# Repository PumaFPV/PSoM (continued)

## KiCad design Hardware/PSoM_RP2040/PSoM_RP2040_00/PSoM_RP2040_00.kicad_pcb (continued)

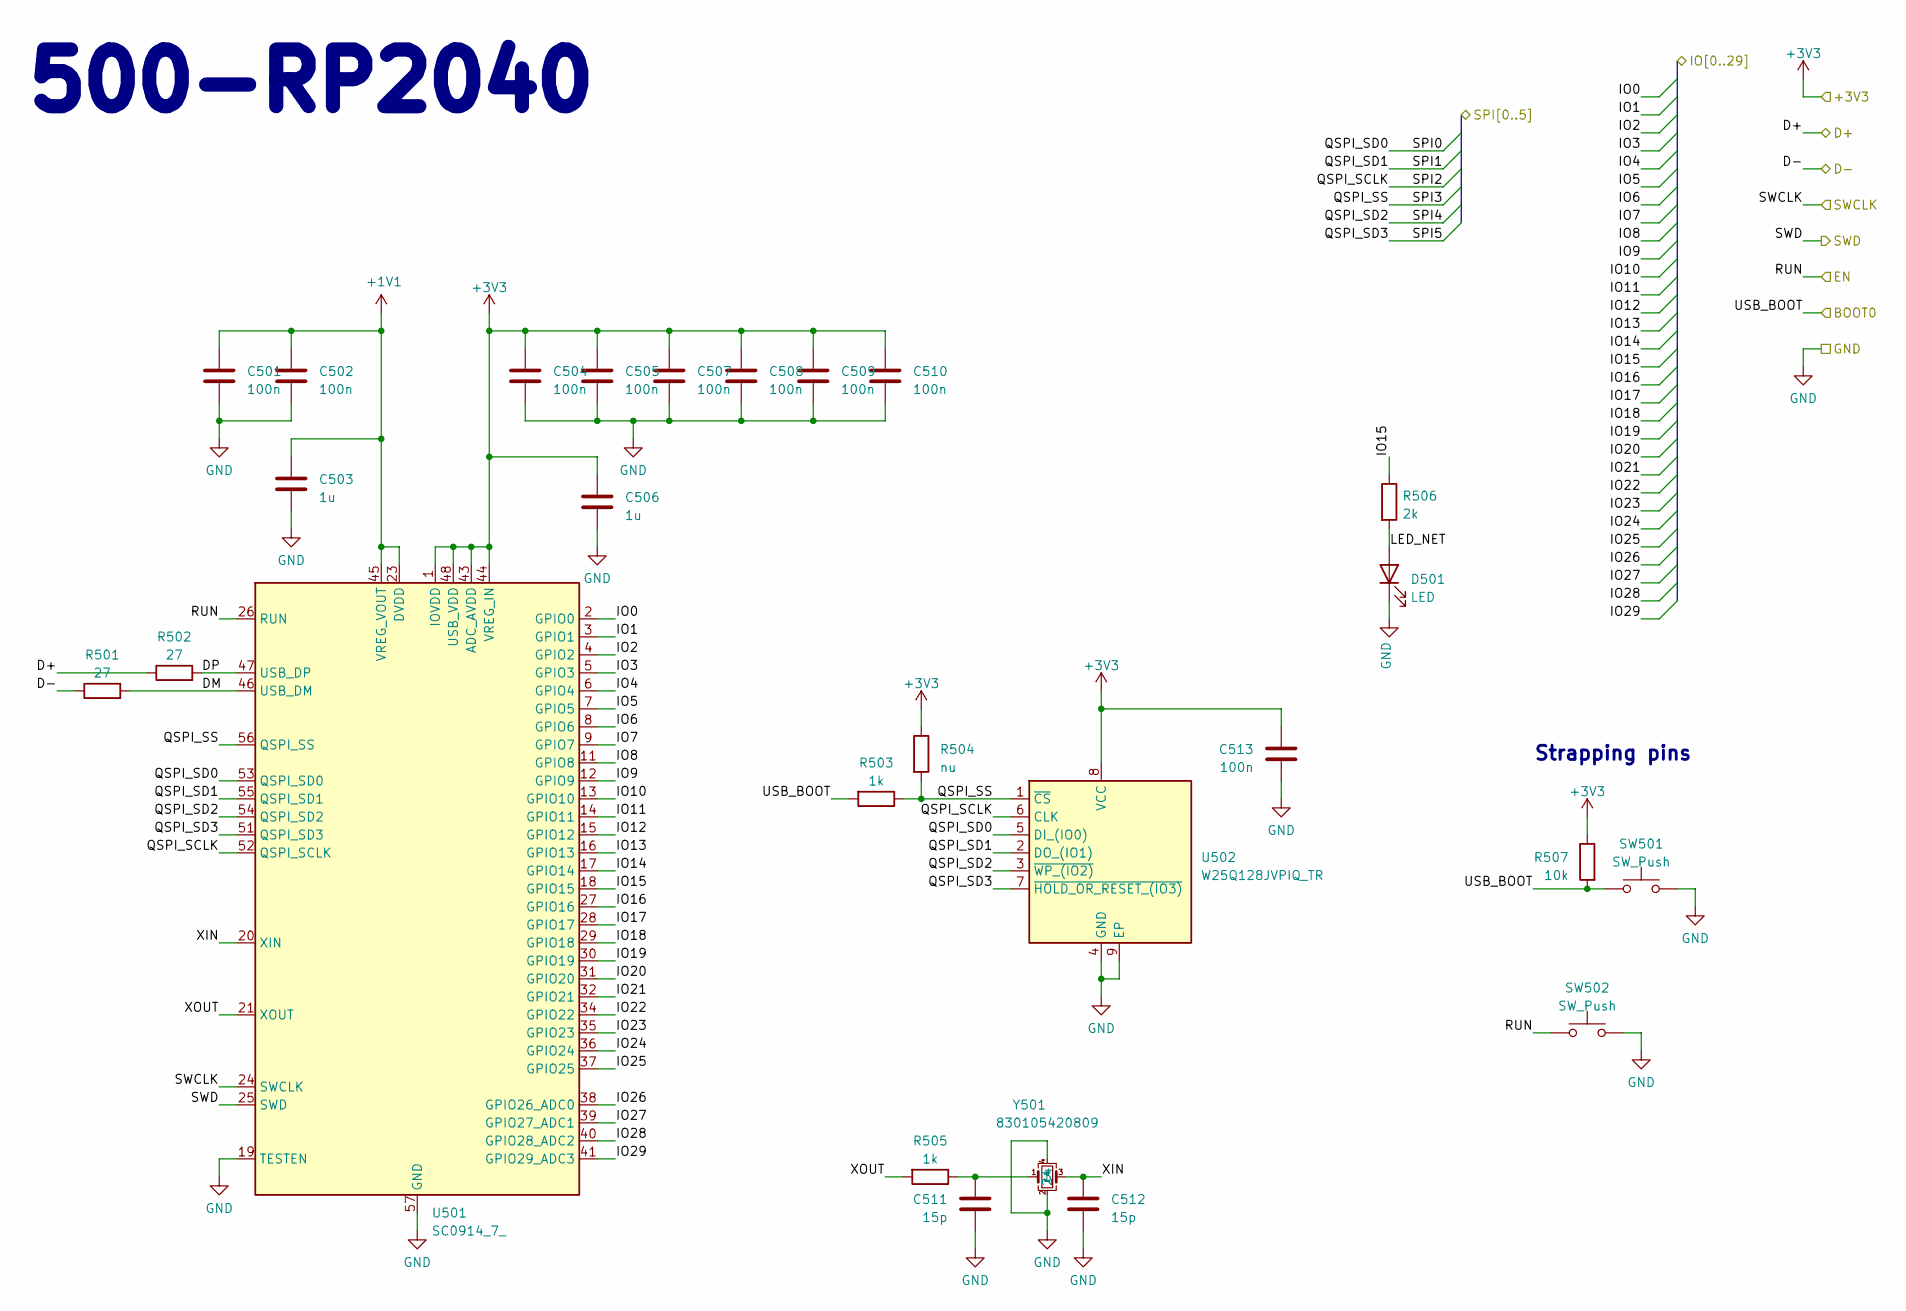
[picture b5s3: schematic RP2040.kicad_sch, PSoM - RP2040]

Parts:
C501, C502, C504, C505, C507, C508, C509, C510, C513: 100n; C_0201_0603Metric
C503, C506: 1u; C_0402_1005Metric
C511, C512: 15p; C_0201_0603Metric
D501: LED; LED_0402_1005Metric
R501, R502: 27; R_0201_0603Metric
R503, R505: 1k; R_0201_0603Metric
R504: nu; R_0201_0603Metric
R506: 2k; R_0402_1005Metric
R507: 10k; R_0201_0603Metric
SW501, SW502: SW_Push; B3U-1000P
U501: SC0914_7_; QFN40P700X700X90-57N-D; Mouser Part Number 358-SC09147
U502: W25Q128JVPIQ_TR; SON127P600X500X80-9N-D; Mouser Part Number 454-W25Q128JVPIQTR
Y501: 830105420809; Mouser Part Number 710-830105420809

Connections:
+1V1: C501.1, C502.1, C503.1, U501.23 (DVDD), U501.45 (VREG_VOUT), U501.50 (DVDD)
+3V3: C504.1, C505.1, C506.1, C507.1, C508.1, C509.1, C510.1, C513.1, R504.1, R507.1, U501.1 (IOVDD), U501.10 (IOVDD), U501.22 (IOVDD), U501.33 (IOVDD), U501.42 (IOVDD), U501.43 (ADC_AVDD), U501.44 (VREG_IN), U501.48 (USB_VDD), U501.49 (IOVDD), U502.8 (VCC); also elsewhere on the board
/200_Connectors/BOOT0: R503.2, R507.2, SW501.1
/200_Connectors/D+: R502.1; also elsewhere on the board
/200_Connectors/D-: R501.1; also elsewhere on the board
/200_Connectors/EN: SW502.1, U501.26 (RUN); also elsewhere on the board
/200_Connectors/SWCLK: U501.24 (SWCLK); also elsewhere on the board
/200_Connectors/SWD: U501.25 (SWD); also elsewhere on the board
/500_RP2040/DM: R501.2, U501.46 (USB_DM)
/500_RP2040/DP: R502.2, U501.47 (USB_DP)
/500_RP2040/LED_NET: D501.2 (A), R506.2
/500_RP2040/XIN: C512.1, U501.20 (XIN), Y501.3
/500_RP2040/XOUT: R505.2, U501.21 (XOUT)
IO0: U501.2 (GPIO0); also elsewhere on the board
IO1: U501.3 (GPIO1); also elsewhere on the board
IO2: U501.4 (GPIO2); also elsewhere on the board
IO3: U501.5 (GPIO3); also elsewhere on the board
IO4: U501.6 (GPIO4); also elsewhere on the board
IO5: U501.7 (GPIO5); also elsewhere on the board
IO6: U501.8 (GPIO6); also elsewhere on the board
IO7: U501.9 (GPIO7); also elsewhere on the board
IO8: U501.11 (GPIO8); also elsewhere on the board
IO9: U501.12 (GPIO9); also elsewhere on the board
IO10: U501.13 (GPIO10); also elsewhere on the board
IO11: U501.14 (GPIO11); also elsewhere on the board
IO12: U501.15 (GPIO12); also elsewhere on the board
IO13: U501.16 (GPIO13); also elsewhere on the board
IO14: U501.17 (GPIO14); also elsewhere on the board
IO15: R506.1, U501.18 (GPIO15); also elsewhere on the board
IO16: U501.27 (GPIO16); also elsewhere on the board
IO17: U501.28 (GPIO17); also elsewhere on the board
IO18: U501.29 (GPIO18); also elsewhere on the board
IO19: U501.30 (GPIO19); also elsewhere on the board
IO20: U501.31 (GPIO20); also elsewhere on the board
IO21: U501.32 (GPIO21); also elsewhere on the board
IO22: U501.34 (GPIO22); also elsewhere on the board
IO23: U501.35 (GPIO23); also elsewhere on the board
IO24: U501.36 (GPIO24); also elsewhere on the board
IO25: U501.37 (GPIO25); also elsewhere on the board
IO26: U501.38 (GPIO26_ADC0); also elsewhere on the board
IO27: U501.39 (GPIO27_ADC1); also elsewhere on the board
IO28: U501.40 (GPIO28_ADC2); also elsewhere on the board
unnamed: C511.1, R505.1, Y501.1
SPI0: U501.53 (QSPI_SD0), U502.5 (DI_(IO0)); also elsewhere on the board
SPI1: U501.55 (QSPI_SD1), U502.2 (DO_(IO1)); also elsewhere on the board
SPI2: U501.52 (QSPI_SCLK), U502.6 (CLK); also elsewhere on the board
SPI3: R503.1, R504.2, U501.56 (QSPI_SS), U502.1 (~CS); also elsewhere on the board
SPI4: U501.54 (QSPI_SD2), U502.3 (~WP_(IO2)); also elsewhere on the board
SPI5: U501.51 (QSPI_SD3), U502.7 (~HOLD_OR_RESET_(IO3)); also elsewhere on the board

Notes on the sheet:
500-RP2040
Strapping pins

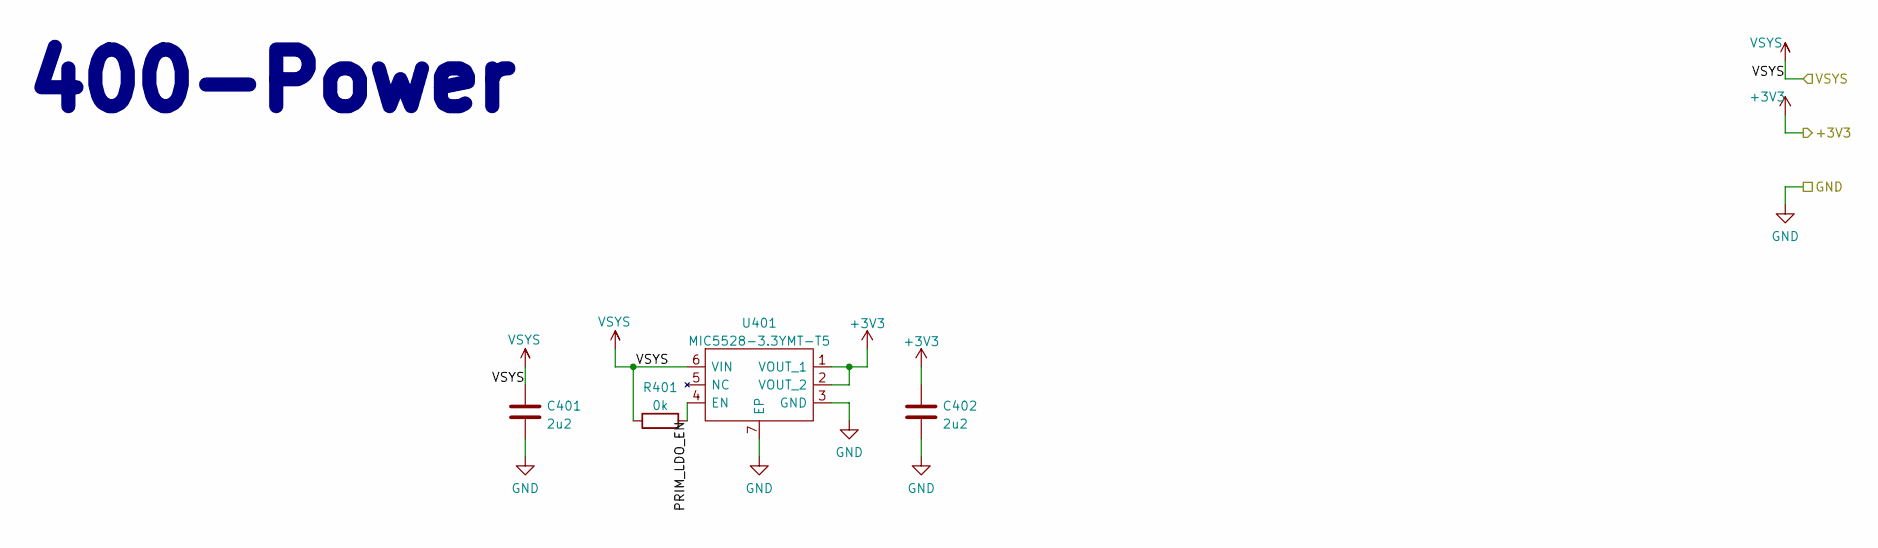
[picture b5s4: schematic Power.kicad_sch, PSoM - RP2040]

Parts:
C401, C402: 2u2; C_0603_1608Metric
R401: 0k; R_0201_0603Metric
U401: MIC5528-3.3YMT-T5; SON40P120X120X60-7N-D; Mouser Part Number 998-MIC5528-3.3YMTT5

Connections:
+3V3: C402.1, U401.1 (VOUT_1), U401.2 (VOUT_2); also elsewhere on the board
/400_Power/PRIM_LDO_EN: R401.2, U401.4 (EN)
/VSYS: C401.1, R401.1, U401.6 (VIN); also elsewhere on the board

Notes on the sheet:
400-Power

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
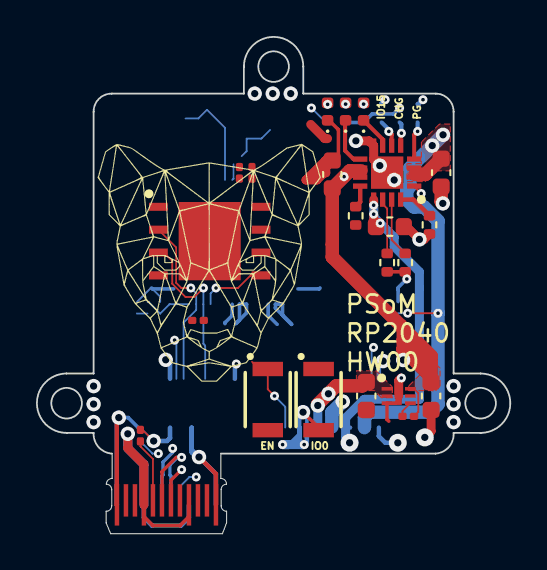
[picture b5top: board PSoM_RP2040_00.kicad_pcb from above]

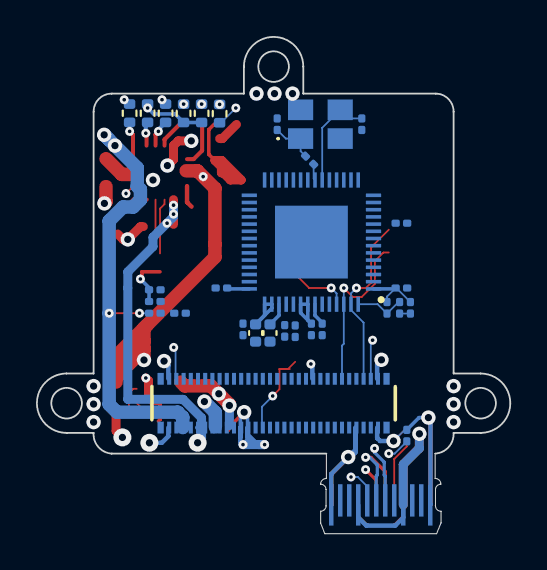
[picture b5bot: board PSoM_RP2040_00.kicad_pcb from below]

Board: 6 copper layers, 26.3 x 27.6 mm, 53 parts (30 on the bottom side), 70 nets.

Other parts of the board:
C201: 100n; C_0201_0603Metric

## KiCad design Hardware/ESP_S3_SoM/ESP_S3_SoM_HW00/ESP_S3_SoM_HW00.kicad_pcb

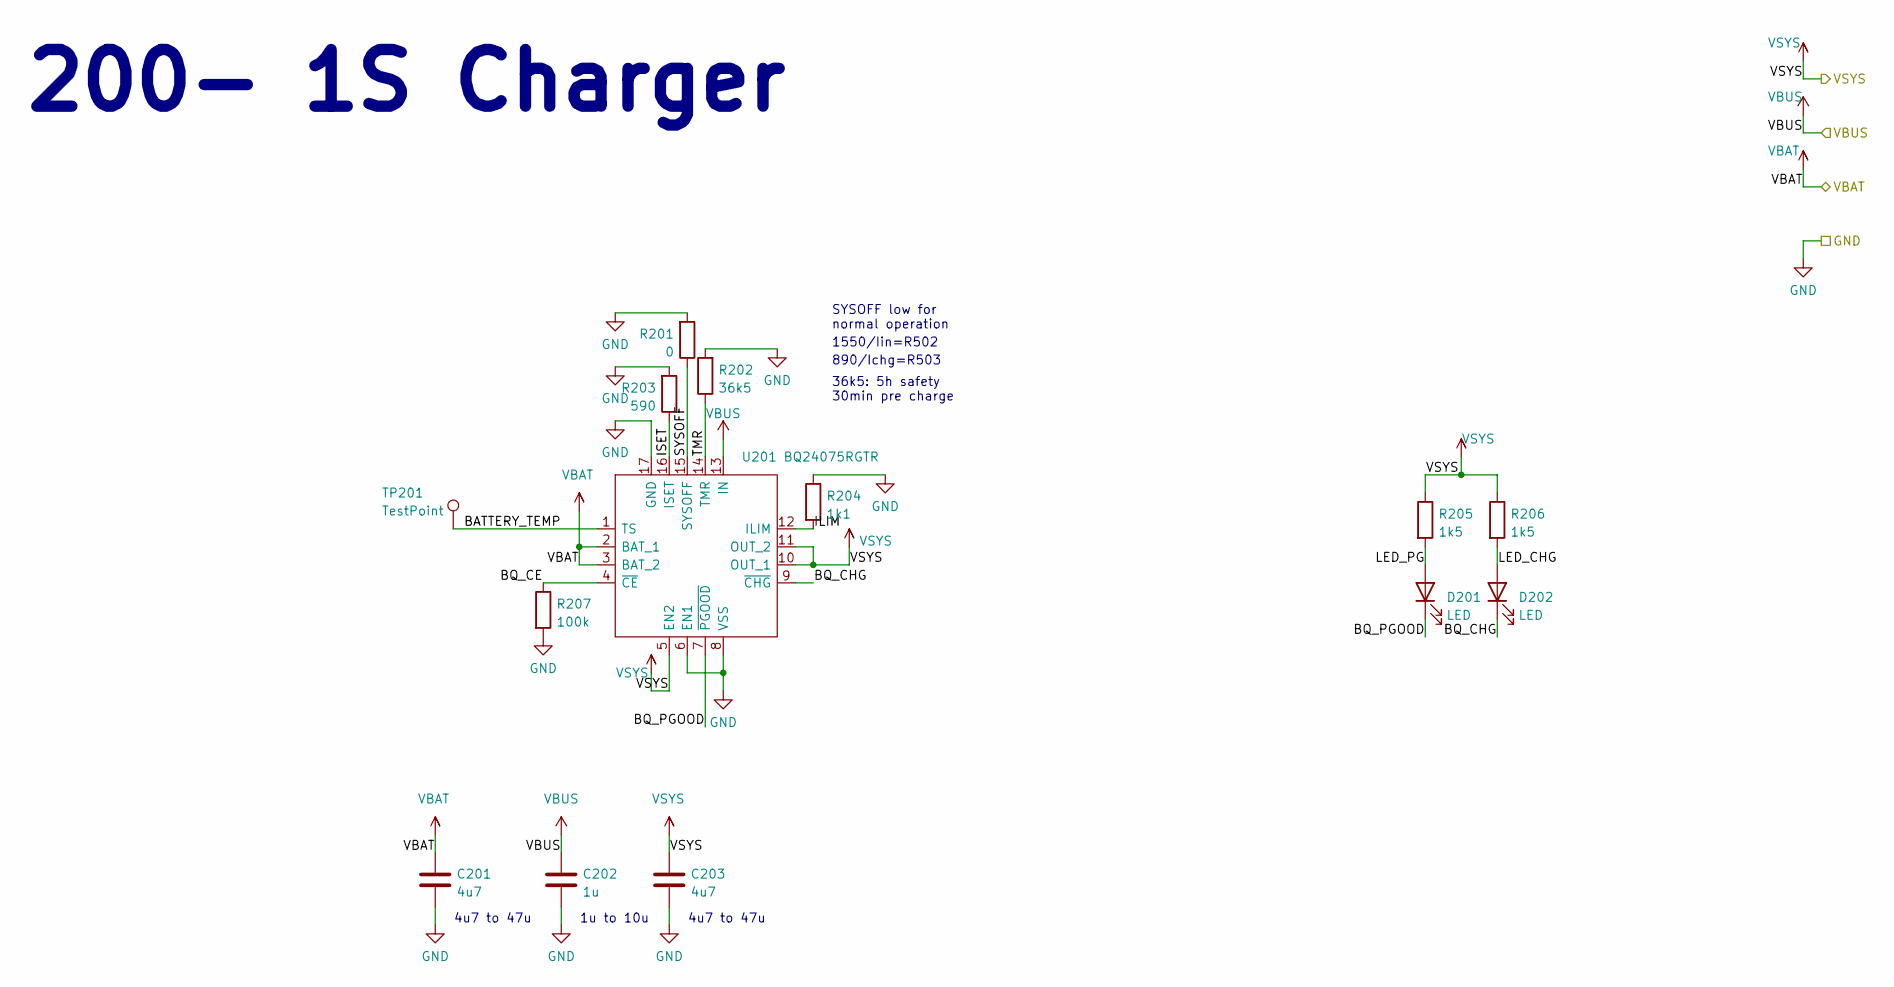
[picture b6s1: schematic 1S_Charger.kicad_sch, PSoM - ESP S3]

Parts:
C201, C203: 4u7; C_0603_1608Metric
C202: 1u; C_0603_1608Metric
D201, D202: LED; LED_0402_1005Metric_DUALSIDE
R201: 0; R_0402_1005Metric
R202: 36k5; R_0402_1005Metric
R203: 590; R_0402_1005Metric
R204: 1k1; R_0402_1005Metric
R205, R206: 1k5; R_0402_1005Metric
R207: 100k; R_0402_1005Metric
TP201: TestPoint; TestPoint_Pad_D1.0mm
U201: BQ24075RGTR; QFN50P300X300X100-17N-D; Mouser Part Number 595-BQ24075RGTR

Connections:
/200_1S_Charger/BATTERY_TEMP: TP201.1, U201.1 (TS)
/200_1S_Charger/BQ_CE: R207.1, U201.4 (~CE)
/200_1S_Charger/BQ_CHG: D202.1 (K), U201.9 (~CHG)
/200_1S_Charger/BQ_PGOOD: D201.1 (K), U201.7 (~PGOOD)
/200_1S_Charger/ILIM: R204.2, U201.12 (ILIM)
/200_1S_Charger/ISET: R203.1, U201.16 (ISET)
/200_1S_Charger/LED_CHG: D202.2 (A), R206.2
/200_1S_Charger/LED_PG: D201.2 (A), R205.2
/200_1S_Charger/SYSOFF: R201.1, U201.15 (SYSOFF)
/200_1S_Charger/TMR: R202.1, U201.14 (TMR)
/200_1S_Charger/VBAT: C201.1, U201.2 (BAT_1), U201.3 (BAT_2)
/200_1S_Charger/VSYS: C203.1, R205.1, R206.1, U201.5 (EN2), U201.10 (OUT_1), U201.11 (OUT_2)
GND: C201.2, C202.2, C203.2, R201.2, R202.2, R203.2, R204.1, R207.2, U201.6 (EN1), U201.8 (VSS), U201.17 (GND); also elsewhere on the board
VBUS: C202.1, U201.13 (IN); also elsewhere on the board

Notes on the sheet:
890/Ichg=R503
200- 1S Charger
4u7 to 47u
1u to 10u
SYSOFF low for normal operation
36k5: 5h safety 30min pre charge
1550/Iin=R502

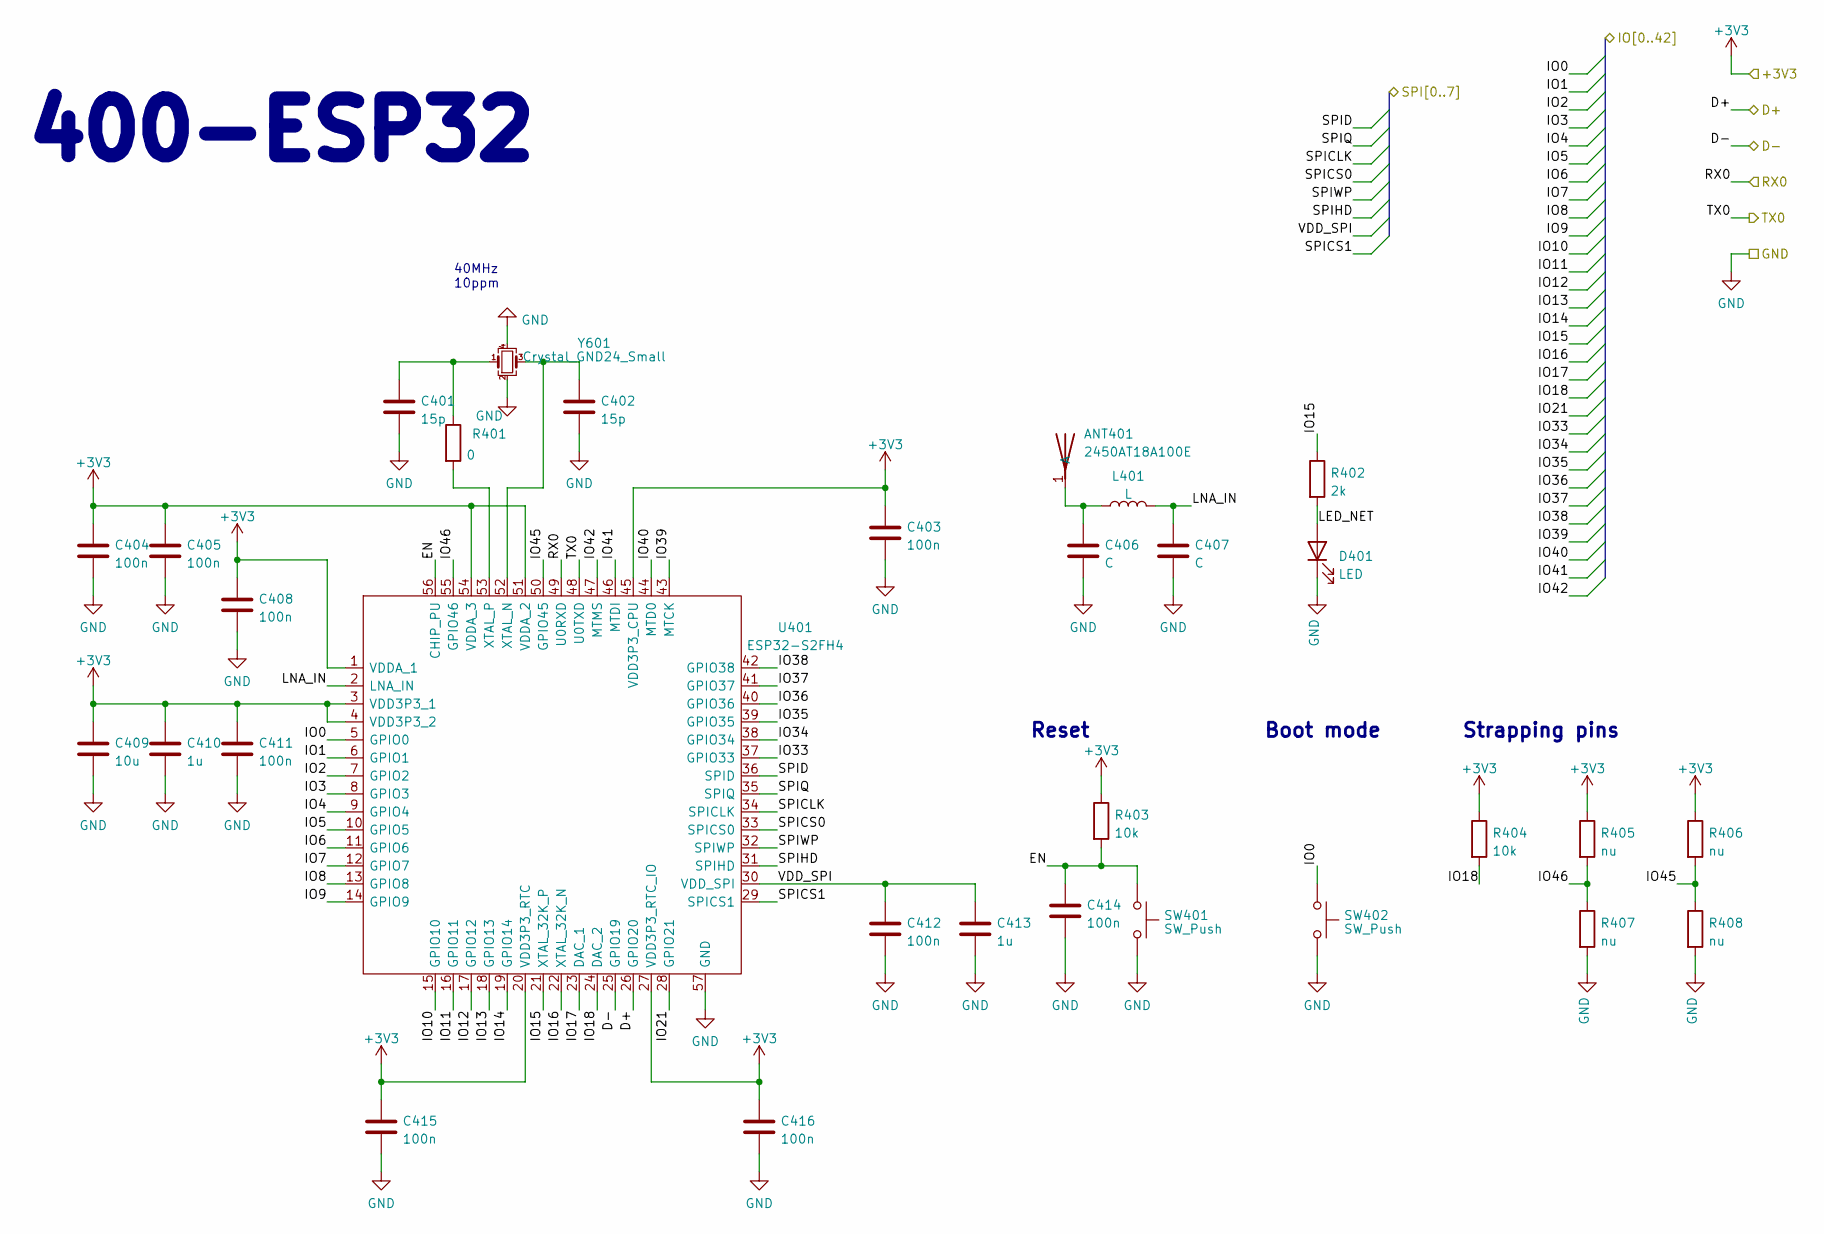
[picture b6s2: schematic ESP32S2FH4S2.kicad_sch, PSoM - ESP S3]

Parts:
ANT401: 2450AT18A100E; ANTC3216X140N; Mouser Part Number 609-2450AT18A100E
C401, C402: 15p; C_0201_0603Metric
C403, C404, C405, C408, C411, C412, C414, C415, C416: 100n; C_0402_1005Metric
C406, C407: C; C_0201_0603Metric
C409: 10u; C_0603_1608Metric
C410, C413: 1u; C_0402_1005Metric
D401: LED; LED_0402_1005Metric_DUALSIDE
L401: L; L_0201_0603Metric
R401: 0; R_0201_0603Metric
R402: 2k; R_0402_1005Metric
R403, R404: 10k; R_0201_0603Metric
R405, R406, R407, R408: nu; R_0201_0603Metric
SW401, SW402: SW_Push; B3U-1000P
U401: ESP32-S2FH4; QFN40P700X700X90-57N-D; Mouser Part Number 356-ESP32-S2FH4
Y601: Crystal_GND24_Small; Crystal_SMD_2016-4Pin_2.0x1.6mm

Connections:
+3V3: C403.1, C404.1, C405.1, C408.1, C409.1, C410.1, C411.1, C415.1, C416.1, R403.1, R404.1, R405.1, R406.1, U401.1 (VDDA_1), U401.3 (VDD3P3_1), U401.4 (VDD3P3_2), U401.20 (VDD3P3_RTC), U401.27 (VDD3P3_RTC_IO), U401.45 (VDD3P3_CPU), U401.51 (VDDA_2), U401.54 (VDDA_3); also elsewhere on the board
/100_Connectors/D+: U401.26 (GPIO20); also elsewhere on the board
/100_Connectors/D-: U401.25 (GPIO19); also elsewhere on the board
/100_Connectors/RX0: U401.49 (U0RXD); also elsewhere on the board
/100_Connectors/TX0: U401.48 (U0TXD); also elsewhere on the board
/400_ESP32/EN: C414.1, R403.2, SW401.1, U401.56 (CHIP_PU)
/400_ESP32/IO45: R406.2, R408.1, U401.50 (GPIO45)
/400_ESP32/IO46: R405.2, R407.1, U401.55 (GPIO46)
/400_ESP32/LED_NET: D401.2 (A), R402.2
/400_ESP32/LNA_IN: C407.1, L401.2, U401.2 (LNA_IN)
/400_ESP32/SPICLK: U401.34 (SPICLK)
/400_ESP32/SPICS0: U401.33 (SPICS0)
/400_ESP32/SPICS1: U401.29 (SPICS1)
/400_ESP32/SPID: U401.36 (SPID)
/400_ESP32/SPIHD: U401.31 (SPIHD)
/400_ESP32/SPIQ: U401.35 (SPIQ)
/400_ESP32/SPIWP: U401.32 (SPIWP)
/400_ESP32/VDD_SPI: C412.1, C413.1, U401.30 (VDD_SPI)
GND: C401.2, C402.2, C403.2, C404.2, C405.2, C406.2, C407.2, C408.2, C409.2, C410.2, C411.2, C412.2, C413.2, C414.2, C415.2, C416.2, D401.1 (K), R407.2, R408.2, SW401.2, SW402.2, U401.57 (GND), Y601.2, Y601.4; also elsewhere on the board
IO0: SW402.1, U401.5 (GPIO0); also elsewhere on the board
IO1: U401.6 (GPIO1); also elsewhere on the board
IO2: U401.7 (GPIO2); also elsewhere on the board
IO3: U401.8 (GPIO3); also elsewhere on the board
IO4: U401.9 (GPIO4); also elsewhere on the board
IO5: U401.10 (GPIO5); also elsewhere on the board
IO6: U401.11 (GPIO6); also elsewhere on the board
IO7: U401.12 (GPIO7); also elsewhere on the board
IO8: U401.13 (GPIO8); also elsewhere on the board
IO9: U401.14 (GPIO9); also elsewhere on the board
IO10: U401.15 (GPIO10); also elsewhere on the board
IO11: U401.16 (GPIO11); also elsewhere on the board
IO12: U401.17 (GPIO12); also elsewhere on the board
IO13: U401.18 (GPIO13); also elsewhere on the board
IO14: U401.19 (GPIO14); also elsewhere on the board
IO15: R402.1, U401.21 (XTAL_32K_P); also elsewhere on the board
IO16: U401.22 (XTAL_32K_N); also elsewhere on the board
IO17: U401.23 (DAC_1); also elsewhere on the board
IO18: R404.2, U401.24 (DAC_2); also elsewhere on the board
IO21: U401.28 (GPIO21); also elsewhere on the board
IO33: U401.37 (GPIO33); also elsewhere on the board
IO34: U401.38 (GPIO34); also elsewhere on the board
IO35: U401.39 (GPIO35); also elsewhere on the board
IO36: U401.40 (GPIO36); also elsewhere on the board
IO37: U401.41 (GPIO37); also elsewhere on the board
IO38: U401.42 (GPIO38); also elsewhere on the board
IO39: U401.43 (MTCK); also elsewhere on the board
IO40: U401.44 (MTD0); also elsewhere on the board
IO41: U401.46 (MTDI); also elsewhere on the board
IO42: U401.47 (MTMS); also elsewhere on the board
unnamed: ANT401.1 (A), C406.1, L401.1
unnamed: C401.1, R401.1, Y601.1
unnamed: C402.1, U401.52 (XTAL_N), Y601.3
unnamed: R401.2, U401.53 (XTAL_P)

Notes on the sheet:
Boot mode
Reset
40MHz 10ppm
400-ESP32
Strapping pins

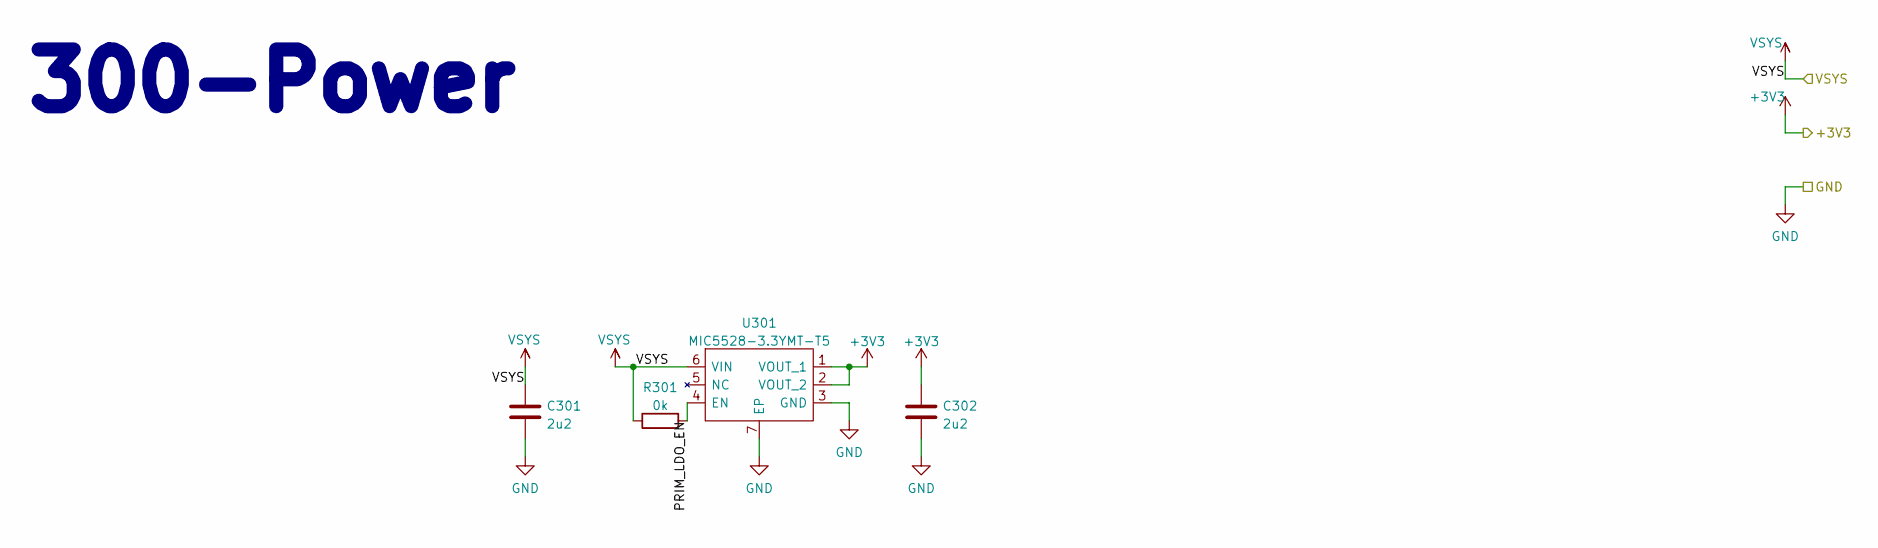
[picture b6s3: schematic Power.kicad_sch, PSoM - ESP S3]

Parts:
C301, C302: 2u2; C_0603_1608Metric
R301: 0k; R_0201_0603Metric
U301: MIC5528-3.3YMT-T5; SON40P120X120X60-7N-D; Mouser Part Number 998-MIC5528-3.3YMTT5

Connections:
+3V3: C302.1, U301.1 (VOUT_1), U301.2 (VOUT_2); also elsewhere on the board
/300_Power/PRIM_LDO_EN: R301.2, U301.4 (EN)
/300_Power/VSYS: C301.1, R301.1, U301.6 (VIN)
GND: C301.2, C302.2, U301.3 (GND), U301.7 (EP); also elsewhere on the board

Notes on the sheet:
300-Power

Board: 2 copper layers, 53 parts (1 on the bottom side), 65 nets, no tracks yet.

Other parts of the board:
J101: USB4510-03-1-A; USB4510031A
J102: 54722-0604; 547220604
R101, R102: 5.1k; R_0201_0603Metric

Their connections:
+3V3: J102.4, J102.6; also elsewhere on the board
/100_Connectors/CC1: J101.A5 (CC1), R102.1
/100_Connectors/CC2: J101.B5 (CC2), R101.1
/100_Connectors/D+: J101.A6 (D+), J101.B6 (D+), J102.58; also elsewhere on the board
/100_Connectors/D-: J101.A7 (D-), J101.B7 (D-), J102.57; also elsewhere on the board
/100_Connectors/RX0: J102.13; also elsewhere on the board
/100_Connectors/TX0: J102.15; also elsewhere on the board
/100_Connectors/VBAT: J102.7, J102.9
/100_Connectors/VSYS: J102.8, J102.10
GND: J101.A1 (GND), J101.A12 (GND), J101.MH1, J101.MH2, J101.MH3, J101.MH4, J102.1, J102.2, J102.11, J102.12, J102.55, J102.56, J102.59, J102.60, R101.2, R102.2; also elsewhere on the board
IO0: J102.14; also elsewhere on the board
IO1: J102.16; also elsewhere on the board
IO2: J102.18; also elsewhere on the board
IO3: J102.20; also elsewhere on the board
IO4: J102.22; also elsewhere on the board
IO5: J102.24; also elsewhere on the board
IO6: J102.26; also elsewhere on the board
IO7: J102.28; also elsewhere on the board
IO8: J102.30; also elsewhere on the board
IO9: J102.32; also elsewhere on the board
IO10: J102.34; also elsewhere on the board
IO11: J102.36; also elsewhere on the board
IO12: J102.38; also elsewhere on the board
IO13: J102.40; also elsewhere on the board
IO14: J102.42; also elsewhere on the board
IO15: J102.44; also elsewhere on the board
IO16: J102.46; also elsewhere on the board
IO17: J102.48; also elsewhere on the board
IO18: J102.50; also elsewhere on the board
IO21: J102.52; also elsewhere on the board
IO33: J102.54; also elsewhere on the board
IO34: J102.37; also elsewhere on the board
IO35: J102.39; also elsewhere on the board
IO36: J102.41; also elsewhere on the board
IO37: J102.43; also elsewhere on the board
IO38: J102.45; also elsewhere on the board
IO39: J102.47; also elsewhere on the board
IO40: J102.49; also elsewhere on the board
IO41: J102.51; also elsewhere on the board
IO42: J102.53; also elsewhere on the board
VBUS: J101.A4 (VBUS), J101.A9 (VBUS), J102.3, J102.5; also elsewhere on the board

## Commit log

2023-04-16 schematic first commit
2023-04-17 moved files
2023-04-17 added SPI Bus
2023-04-18 working on schematic
2023-04-25 lots of work on routing
2023-04-28 led footprint update
2023-04-28 working on routing
2023-12-27 Started nRF52
2024-01-21 Working on PSoM ESP32S2
2024-01-28 Routing ESP32S2
2024-01-28 Continue work on routing
2024-01-28 Routing again
2024-01-31 Little backup before messing up everything
2024-01-31 ESP32 data is done
2024-02-03 working on power routing
2024-02-05 Routing is done
2024-02-05 Routing done, ready for prod
2024-02-06 quick pinout adjustement
2024-02-08 Added mecha export from PCB
2024-02-15 exported pcb fab
2024-02-20 updated prod files + holes are M1.6
2024-02-21 Started PSoM RP2040
2024-02-25 made small mecha adjustement
2024-02-26 final esp32s2 update?
2024-02-28 Saved produced files
2024-02-28 updated bas de page
2024-03-03 added nrf52840
2024-03-06 added stencil holder
2024-03-06 updated stencil support
2024-03-18 Adding PICO_D4 SoM
    Created from ESP32S2 project
    Modifying schematics
    Adding specific documentation
2024-03-26 Small cartouche mistake
2024-03-26 small adjustements on rp2040 routing
2024-03-31 started pinout file
2024-04-14 First version of schematic Connections
    Done according to definition in pinout.xlsx (available on master)
    Renaming ESP_... to ESP32_...
2024-08-19 exported step
2024-09-30 started nrf52 schematic
2024-10-01 nrf schematic ongoing
2024-10-02 added quartz + matching circuit for nrf52 psom
2024-10-08 power organisation thinking
2024-10-09 updated ESP32_PICO_D4 schematic page
2024-10-13 Final pinout for PSoM_ESP32_PICO_D4
2024-10-13 Unifying naming
2024-10-21 working on nrf52840
2024-10-22 updated nFR52840 power diagram
2024-11-07 footprint assignement done
2024-11-19 added nfc connector + update pinout info
2025-02-02 First route for the PICO_D4
    Added .gitignore
    Modify at your own taste, this one will be tricky
2025-02-05 IO routes finished
    Still missing the routes for GND and 3.3V
    Tried to adjust the .gitignore, experimental
2025-02-06 moved in the nrf inside of boundries
2025-02-07 routing is doing great progress
2025-02-07 moved a few traces
2025-02-07 schematic should be done
2025-02-09 working on the routing
2025-02-09 Officially finished first version of PicoD4 PSoM
    Modified .gitignore
2025-02-09 just a cleanup
2025-02-09 pico d4 routage terminé?
2025-02-10 nrf52 routing
2025-02-10 done for today
2025-02-10 moved the nrf away from the npm
2025-02-10 moved the nrf away and re routed everything
2025-02-11 TODO: RF and GND vias
2025-02-11 havent done much routing here
2025-02-11 rf routing to do
2025-02-11 still need to do rf
2025-02-13 opened ground plane for antenna
2025-02-14 added ufl connector and trace width for 50ohm rf
2025-02-18 finished routing + generated gerbers
2025-02-19 did some optimization on nrf52840_00
2025-03-11 added pico d4 production files
2025-06-24 started schematic for PSoM_Carrier_00
2025-06-25 finished schematic started layout
2025-06-26 routing v0 is done
2025-06-28 updated routing
2025-06-30 routing done, exported gerber file
